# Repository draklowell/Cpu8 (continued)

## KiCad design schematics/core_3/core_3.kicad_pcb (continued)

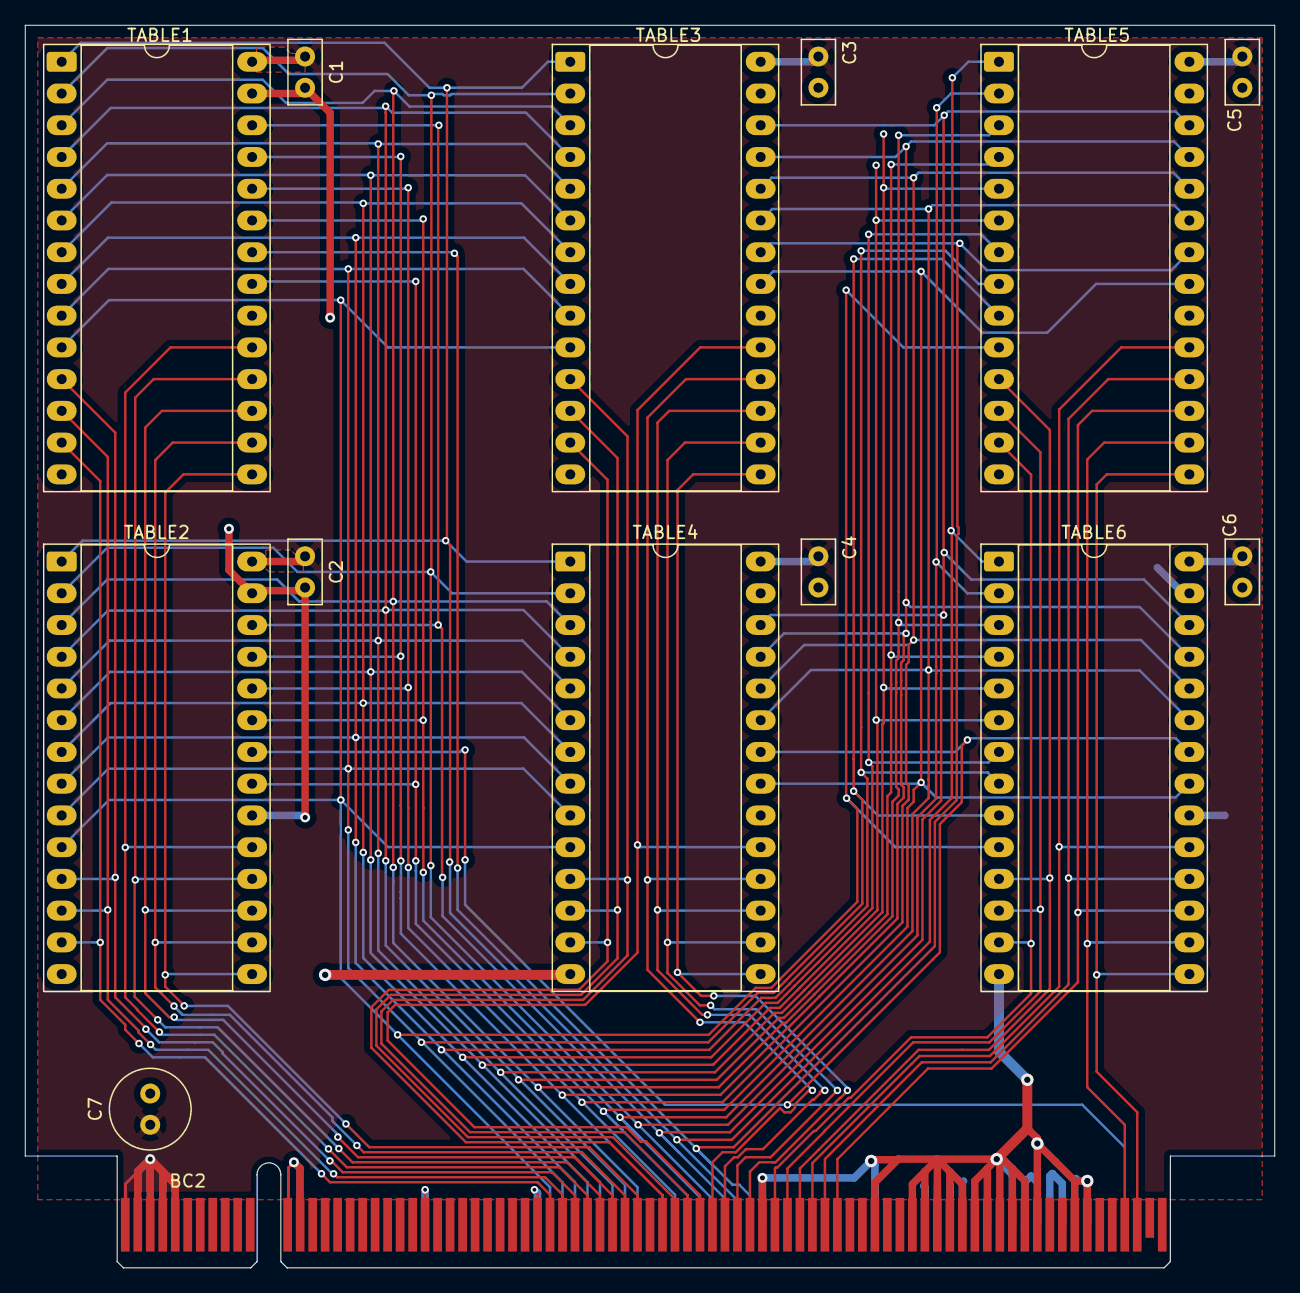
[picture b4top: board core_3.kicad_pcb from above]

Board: 2 copper layers, 100.0 x 99.4 mm, 14 parts (0 on the bottom side), 43 nets.

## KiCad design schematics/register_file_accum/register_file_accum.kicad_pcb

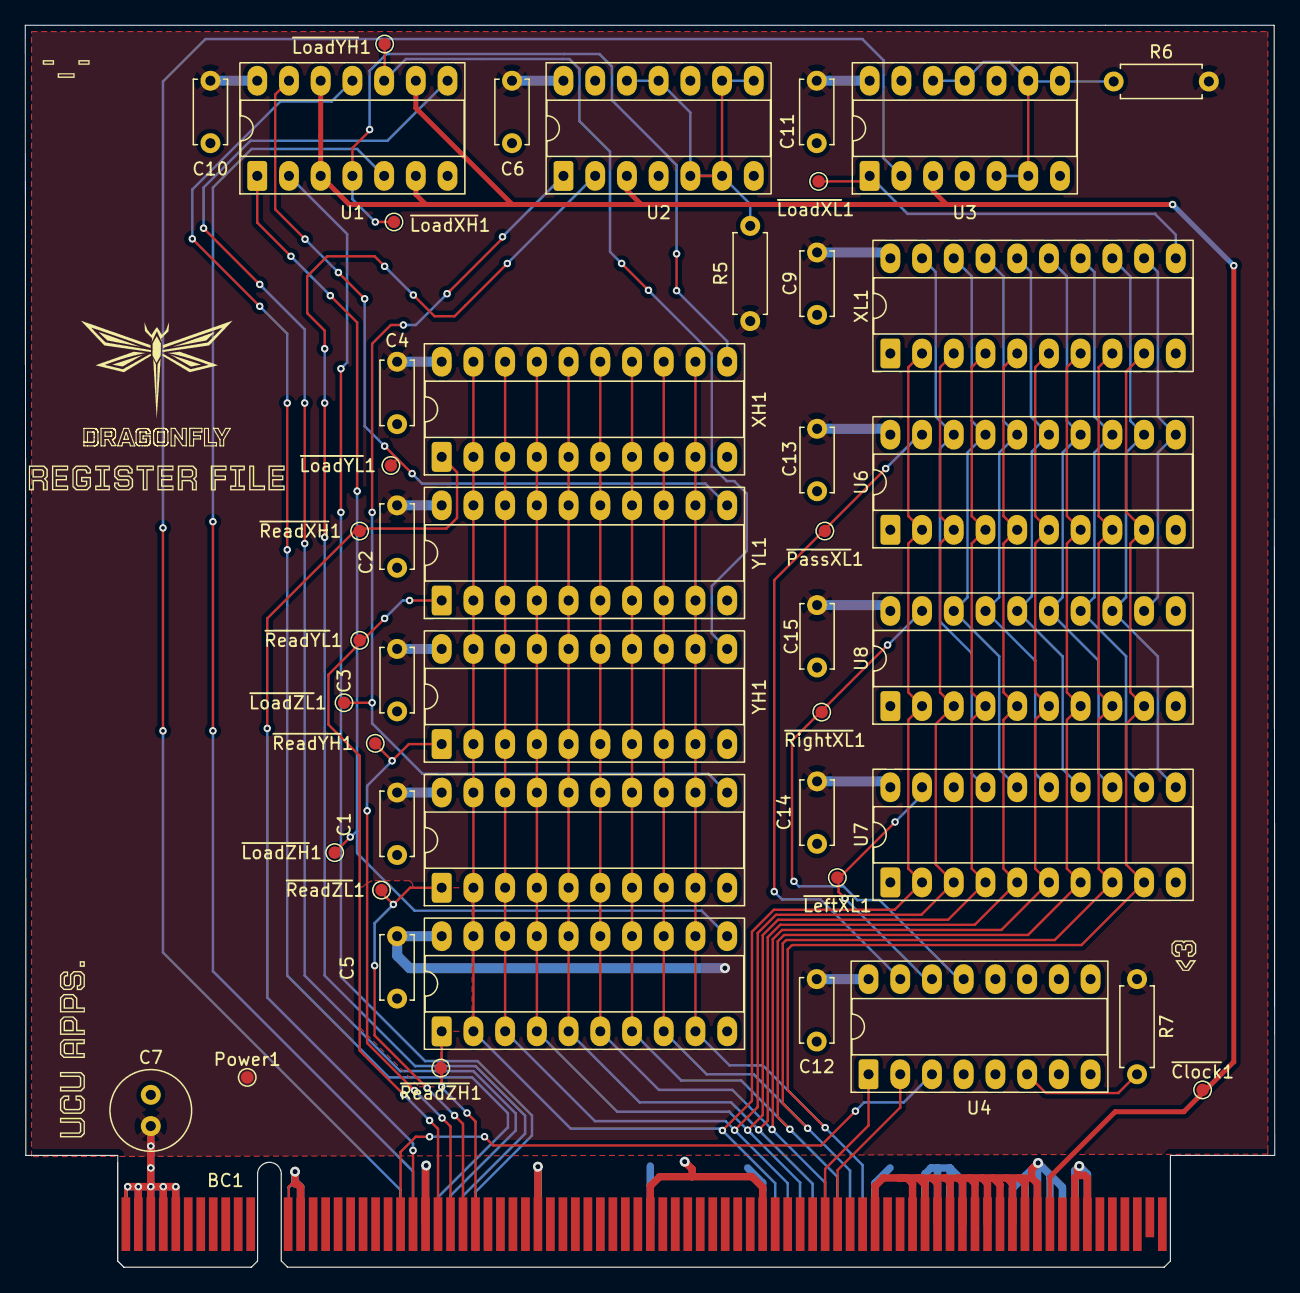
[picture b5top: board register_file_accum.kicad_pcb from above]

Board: 2 copper layers, 100.1 x 99.4 mm, 36 parts (0 on the bottom side), 45 nets.

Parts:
BC1: BusConnector; BUS_PCIexpress_x16
C1, C2, C3, C4, C5, C6, C9, C10, C11, C12, C13, C14, C15: C; C_Disc_D5.0mm_W2.5mm_P5.00mm
C7: C; C_Radial_D6.3mm_H5.0mm_P2.50mm
Power1: Power; TestPoint_Pad_D1.0mm
R5, R6, R7: R; R_Axial_DIN0207_L6.3mm_D2.5mm_P7.62mm_Horizontal
U1, U2, U3: 74LS02; DIP-14_W7.62mm_Socket_LongPads
U4: 74LS138; DIP-16_W7.62mm_Socket_LongPads
U6, U7, U8: 74LS245; DIP-20_W7.62mm_Socket_LongPads
XH1: 74LS574; DIP-20_W7.62mm_Socket_LongPads
XL1: 74LS574; DIP-20_W7.62mm_Socket_LongPads
YH1: 74LS574; DIP-20_W7.62mm_Socket_LongPads
YL1: 74LS574; DIP-20_W7.62mm_Socket_LongPads
ZH1: 74LS574; DIP-20_W7.62mm_Socket_LongPads
ZL1: 74LS574; DIP-20_W7.62mm_Socket_LongPads
kibuzzard-691DE1A7: G***; kibuzzard-691DE1A7
kibuzzard-691DE1B7: G***; kibuzzard-691DE1B7
kibuzzard-691DE19C: G***; kibuzzard-691DE19C
kibuzzard-6911B41A: G***; kibuzzard-6911B41A

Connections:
/ACCUM0: U6.18 (B0), U7.17 (B1), XL1.19 (Q0)
/ACCUM1: U6.17 (B1), U7.16 (B2), U8.18 (B0), XL1.18 (Q1)
/ACCUM2: U6.16 (B2), U7.15 (B3), U8.17 (B1), XL1.17 (Q2)
/ACCUM3: U6.15 (B3), U7.14 (B4), U8.16 (B2), XL1.16 (Q3)
/ACCUM4: U6.14 (B4), U7.13 (B5), U8.15 (B3), XL1.15 (Q4)
/ACCUM5: U6.13 (B5), U7.12 (B6), U8.14 (B4), XL1.14 (Q5)
/ACCUM6: U6.12 (B6), U7.11 (B7), U8.13 (B5), XL1.13 (Q6)
/ACCUM7: U6.11 (B7), U8.12 (B6), XL1.12 (Q7)
/ACSHLEFT: U4.14 (O1), U7.19 (CE)
/ACSHRIGHT: U4.13 (O2), U8.19 (CE)
/DATA0: BC1.A51 (DATA0), U6.2 (A0), U7.2 (A0), U8.2 (A0), XH1.2 (D0), XH1.19 (Q0), XL1.2 (D0), YH1.2 (D0), YH1.19 (Q0), YL1.2 (D0), YL1.19 (Q0), ZH1.2 (D0), ZH1.19 (Q0), ZL1.2 (D0), ZL1.19 (Q0)
/DATA1: BC1.A52 (DATA1), U6.3 (A1), U7.3 (A1), U8.3 (A1), XH1.3 (D1), XH1.18 (Q1), XL1.3 (D1), YH1.3 (D1), YH1.18 (Q1), YL1.3 (D1), YL1.18 (Q1), ZH1.3 (D1), ZH1.18 (Q1), ZL1.3 (D1), ZL1.18 (Q1)
/DATA2: BC1.A53 (DATA2), U6.4 (A2), U7.4 (A2), U8.4 (A2), XH1.4 (D2), XH1.17 (Q2), XL1.4 (D2), YH1.4 (D2), YH1.17 (Q2), YL1.4 (D2), YL1.17 (Q2), ZH1.4 (D2), ZH1.17 (Q2), ZL1.4 (D2), ZL1.17 (Q2)
/DATA3: BC1.A54 (DATA3), U6.5 (A3), U7.5 (A3), U8.5 (A3), XH1.5 (D3), XH1.16 (Q3), XL1.5 (D3), YH1.5 (D3), YH1.16 (Q3), YL1.5 (D3), YL1.16 (Q3), ZH1.5 (D3), ZH1.16 (Q3), ZL1.5 (D3), ZL1.16 (Q3)
/DATA4: BC1.A55 (DATA4), U6.6 (A4), U7.6 (A4), U8.6 (A4), XH1.6 (D4), XH1.15 (Q4), XL1.6 (D4), YH1.6 (D4), YH1.15 (Q4), YL1.6 (D4), YL1.15 (Q4), ZH1.6 (D4), ZH1.15 (Q4), ZL1.6 (D4), ZL1.15 (Q4)
/DATA5: BC1.A56 (DATA5), U6.7 (A5), U7.7 (A5), U8.7 (A5), XH1.7 (D5), XH1.14 (Q5), XL1.7 (D5), YH1.7 (D5), YH1.14 (Q5), YL1.7 (D5), YL1.14 (Q5), ZH1.7 (D5), ZH1.14 (Q5), ZL1.7 (D5), ZL1.14 (Q5)
/DATA6: BC1.A57 (DATA6), U6.8 (A6), U7.8 (A6), U8.8 (A6), XH1.8 (D6), XH1.13 (Q6), XL1.8 (D6), YH1.8 (D6), YH1.13 (Q6), YL1.8 (D6), YL1.13 (Q6), ZH1.8 (D6), ZH1.13 (Q6), ZL1.8 (D6), ZL1.13 (Q6)
/DATA7: BC1.A58 (DATA7), U6.9 (A7), U7.9 (A7), U8.9 (A7), XH1.9 (D7), XH1.12 (Q7), XL1.9 (D7), YH1.9 (D7), YH1.12 (Q7), YL1.9 (D7), YL1.12 (Q7), ZH1.9 (D7), ZH1.12 (Q7), ZL1.9 (D7), ZL1.12 (Q7)
/LAC: BC1.A21 (~LAC), U3.2
/SHL: BC1.B55 (ACSHLEFT), U4.1 (A0)
/SHR: BC1.B56 (ACSHRIGHT), U4.2 (A1)
/~CLK: BC1.B73 (~CLK), U1.3, U1.6, U1.9, U1.12, U2.3, U3.3
/~PASS: BC1.B21 (~RAC), U4.3 (A2)
/~RAC: U4.15 (O0), U6.19 (CE)
GND: BC1.A12 (GND), BC1.A13 (GND), BC1.A23 (GND), BC1.A32 (GND), BC1.A41 (GND), BC1.A50 (GND), BC1.A59 (GND), BC1.A63 (GND), BC1.A64 (GND), BC1.A65 (GND), BC1.A66 (GND), BC1.A70 (GND), BC1.A71 (GND), BC1.A72 (GND), BC1.A73 (GND), BC1.A74 (GND), BC1.A75 (GND), BC1.A76 (GND), BC1.B12 (GND), BC1.B13 (GND), BC1.B23 (GND), BC1.B32 (GND), BC1.B41 (GND), BC1.B50 (GND), BC1.B59 (GND), BC1.B62 (GND), BC1.B63 (GND), BC1.B64 (GND), BC1.B65 (GND), BC1.B66 (GND), BC1.B67 (GND), BC1.B68 (GND), BC1.B69 (GND), BC1.B70 (GND), BC1.B71 (GND), BC1.B72 (GND), BC1.B75 (GND), BC1.B76 (GND), C1.1, C2.1, C3.1, C4.1, C5.1, C6.2, C7.2, C9.2, C10.2, C11.2, C12.2, C13.2, C14.2, C15.2, U1.7 (GND), U2.7 (GND), U3.7 (GND), U4.4 (E1), U4.5 (E2), U4.8 (GND), U6.1 (A->B), U6.10 (GND), U7.1 (A->B), U7.10 (GND), U7.18 (B0), U8.1 (A->B), U8.10 (GND), U8.11 (B7), XH1.10 (GND), XL1.1 (OE), XL1.10 (GND), YH1.10 (GND), YL1.10 (GND), ZH1.10 (GND), ZL1.10 (GND)
unnamed: BC1.A22 (~LXH), U1.5
unnamed: BC1.A25 (~LYH), U1.8
unnamed: BC1.A24 (~LYL), U1.11
unnamed: BC1.A27 (~LZH), U1.2
unnamed: BC1.A26 (~LZL), U2.2
unnamed: BC1.B22 (~RXH), XH1.1 (OE)
unnamed: BC1.B25 (~RYH), YH1.1 (OE)
unnamed: BC1.B24 (~RYL), YL1.1 (OE)
unnamed: BC1.B27 (~RZH), ZH1.1 (OE)
unnamed: BC1.B26 (~RZL), ZL1.1 (OE)
unnamed: R5.2, U2.5, U2.6, U2.8, U2.9, U2.11, U2.12
unnamed: R6.1, U3.5, U3.6, U3.8, U3.9, U3.11, U3.12
unnamed: R7.2, U4.6 (E3)
unnamed: U1.4, XH1.11 (Cp)
unnamed: U3.1, XL1.11 (Cp)
unnamed: U1.10, YH1.11 (Cp)
unnamed: U1.13, YL1.11 (Cp)
unnamed: U1.1, ZH1.11 (Cp)
unnamed: U2.1, ZL1.11 (Cp)
VCC: BC1.A1 (VCC), BC1.A2 (VCC), BC1.A3 (VCC), BC1.A4 (VCC), BC1.A5 (VCC), BC1.B1 (VCC), BC1.B2 (VCC), BC1.B3 (VCC), BC1.B4 (VCC), BC1.B5 (VCC), C1.2, C2.2, C3.2, C4.2, C5.2, C6.1, C7.1, C9.1, C10.1, C11.1, C12.1, C13.1, C14.1, C15.1, Power1.1, R5.1, R6.2, R7.1, U1.14 (VCC), U2.14 (VCC), U3.14 (VCC), U4.16 (VCC), U6.20 (VCC), U7.20 (VCC), U8.20 (VCC), XH1.20 (VCC), XL1.20 (VCC), YH1.20 (VCC), YL1.20 (VCC), ZH1.20 (VCC), ZL1.20 (VCC)

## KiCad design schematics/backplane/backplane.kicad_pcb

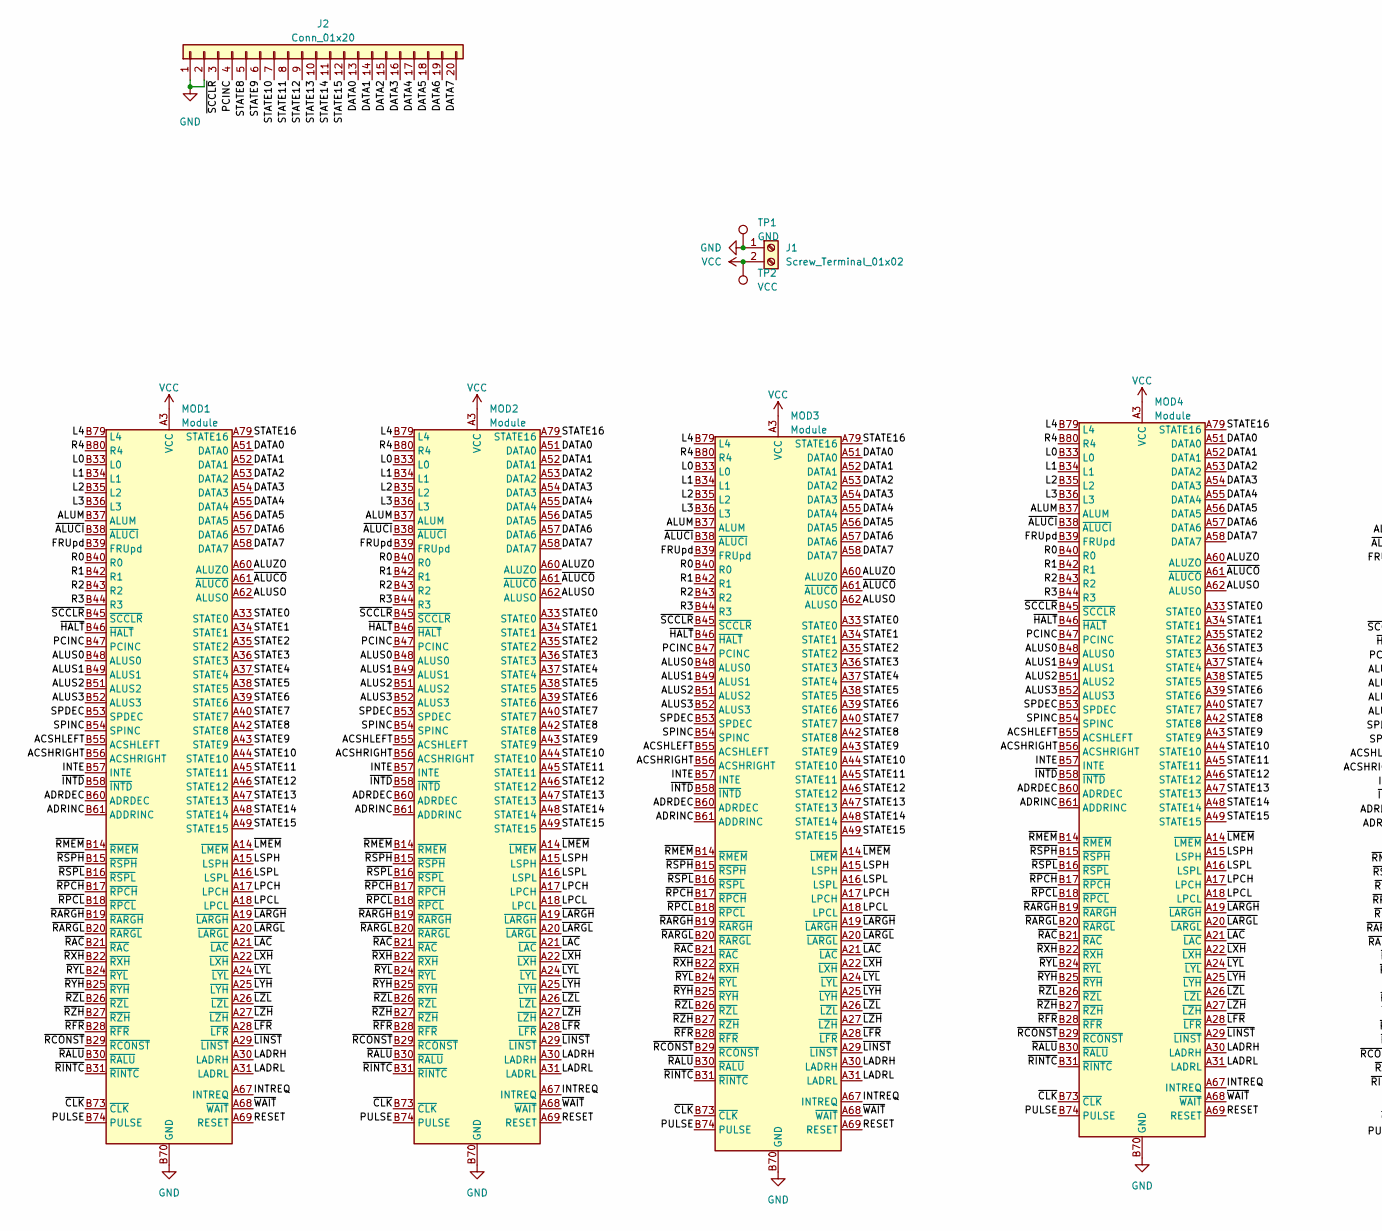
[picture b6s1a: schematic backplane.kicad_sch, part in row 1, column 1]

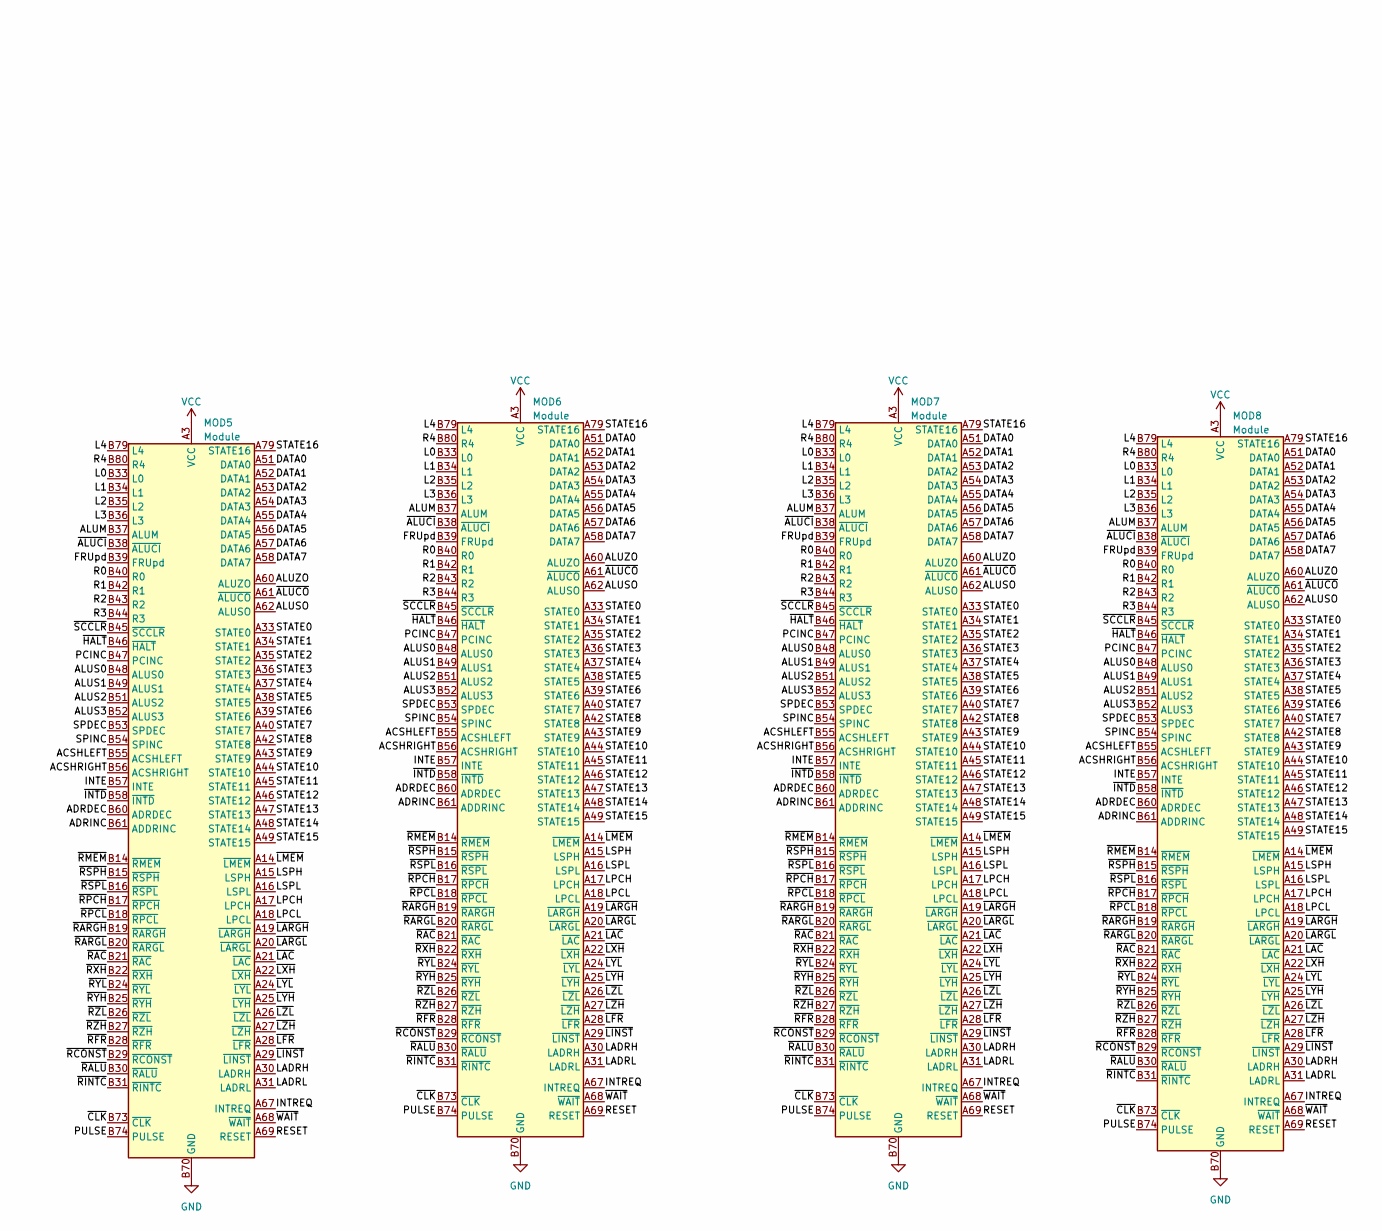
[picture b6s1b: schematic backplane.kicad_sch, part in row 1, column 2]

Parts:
J1: Screw_Terminal_01x02; SHDR2W100P0X500_1X2_1000X780X1020P
J2: Conn_01x20; PinSocket_1x20_P2.54mm_Vertical
MOD1, MOD2, MOD3, MOD4, MOD5, MOD6, MOD7, MOD8: Module; BusSlot
TP1: GND; TestPoint_Pad_D1.5mm
TP2: VCC; TestPoint_Pad_D1.5mm

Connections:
/ACSHLEFT: MOD1.B55 (ACSHLEFT), MOD2.B55 (ACSHLEFT), MOD3.B55 (ACSHLEFT), MOD4.B55 (ACSHLEFT), MOD5.B55 (ACSHLEFT), MOD6.B55 (ACSHLEFT), MOD7.B55 (ACSHLEFT), MOD8.B55 (ACSHLEFT)
/ACSHRIGHT: MOD1.B56 (ACSHRIGHT), MOD2.B56 (ACSHRIGHT), MOD3.B56 (ACSHRIGHT), MOD4.B56 (ACSHRIGHT), MOD5.B56 (ACSHRIGHT), MOD6.B56 (ACSHRIGHT), MOD7.B56 (ACSHRIGHT), MOD8.B56 (ACSHRIGHT)
/ADRDEC: MOD1.B60 (ADRDEC), MOD2.B60 (ADRDEC), MOD3.B60 (ADRDEC), MOD4.B60 (ADRDEC), MOD5.B60 (ADRDEC), MOD6.B60 (ADRDEC), MOD7.B60 (ADRDEC), MOD8.B60 (ADRDEC)
/ADRINC: MOD1.B61 (ADDRINC), MOD2.B61 (ADDRINC), MOD3.B61 (ADDRINC), MOD4.B61 (ADDRINC), MOD5.B61 (ADDRINC), MOD6.B61 (ADDRINC), MOD7.B61 (ADDRINC), MOD8.B61 (ADDRINC)
/ALUM: MOD1.B37 (ALUM), MOD2.B37 (ALUM), MOD3.B37 (ALUM), MOD4.B37 (ALUM), MOD5.B37 (ALUM), MOD6.B37 (ALUM), MOD7.B37 (ALUM), MOD8.B37 (ALUM)
/ALUS0: MOD1.B48 (ALUS0), MOD2.B48 (ALUS0), MOD3.B48 (ALUS0), MOD4.B48 (ALUS0), MOD5.B48 (ALUS0), MOD6.B48 (ALUS0), MOD7.B48 (ALUS0), MOD8.B48 (ALUS0)
/ALUS1: MOD1.B49 (ALUS1), MOD2.B49 (ALUS1), MOD3.B49 (ALUS1), MOD4.B49 (ALUS1), MOD5.B49 (ALUS1), MOD6.B49 (ALUS1), MOD7.B49 (ALUS1), MOD8.B49 (ALUS1)
/ALUS2: MOD1.B51 (ALUS2), MOD2.B51 (ALUS2), MOD3.B51 (ALUS2), MOD4.B51 (ALUS2), MOD5.B51 (ALUS2), MOD6.B51 (ALUS2), MOD7.B51 (ALUS2), MOD8.B51 (ALUS2)
/ALUS3: MOD1.B52 (ALUS3), MOD2.B52 (ALUS3), MOD3.B52 (ALUS3), MOD4.B52 (ALUS3), MOD5.B52 (ALUS3), MOD6.B52 (ALUS3), MOD7.B52 (ALUS3), MOD8.B52 (ALUS3)
/ALUSO: MOD1.A62 (ALUSO), MOD2.A62 (ALUSO), MOD3.A62 (ALUSO), MOD4.A62 (ALUSO), MOD5.A62 (ALUSO), MOD6.A62 (ALUSO), MOD7.A62 (ALUSO), MOD8.A62 (ALUSO)
/ALUZO: MOD1.A60 (ALUZO), MOD2.A60 (ALUZO), MOD3.A60 (ALUZO), MOD4.A60 (ALUZO), MOD5.A60 (ALUZO), MOD6.A60 (ALUZO), MOD7.A60 (ALUZO), MOD8.A60 (ALUZO)
/DATA0: J2.13, MOD1.A51 (DATA0), MOD2.A51 (DATA0), MOD3.A51 (DATA0), MOD4.A51 (DATA0), MOD5.A51 (DATA0), MOD6.A51 (DATA0), MOD7.A51 (DATA0), MOD8.A51 (DATA0)
/DATA1: J2.14, MOD1.A52 (DATA1), MOD2.A52 (DATA1), MOD3.A52 (DATA1), MOD4.A52 (DATA1), MOD5.A52 (DATA1), MOD6.A52 (DATA1), MOD7.A52 (DATA1), MOD8.A52 (DATA1)
/DATA2: J2.15, MOD1.A53 (DATA2), MOD2.A53 (DATA2), MOD3.A53 (DATA2), MOD4.A53 (DATA2), MOD5.A53 (DATA2), MOD6.A53 (DATA2), MOD7.A53 (DATA2), MOD8.A53 (DATA2)
/DATA3: J2.16, MOD1.A54 (DATA3), MOD2.A54 (DATA3), MOD3.A54 (DATA3), MOD4.A54 (DATA3), MOD5.A54 (DATA3), MOD6.A54 (DATA3), MOD7.A54 (DATA3), MOD8.A54 (DATA3)
/DATA4: J2.17, MOD1.A55 (DATA4), MOD2.A55 (DATA4), MOD3.A55 (DATA4), MOD4.A55 (DATA4), MOD5.A55 (DATA4), MOD6.A55 (DATA4), MOD7.A55 (DATA4), MOD8.A55 (DATA4)
/DATA5: J2.18, MOD1.A56 (DATA5), MOD2.A56 (DATA5), MOD3.A56 (DATA5), MOD4.A56 (DATA5), MOD5.A56 (DATA5), MOD6.A56 (DATA5), MOD7.A56 (DATA5), MOD8.A56 (DATA5)
/DATA6: J2.19, MOD1.A57 (DATA6), MOD2.A57 (DATA6), MOD3.A57 (DATA6), MOD4.A57 (DATA6), MOD5.A57 (DATA6), MOD6.A57 (DATA6), MOD7.A57 (DATA6), MOD8.A57 (DATA6)
/DATA7: J2.20, MOD1.A58 (DATA7), MOD2.A58 (DATA7), MOD3.A58 (DATA7), MOD4.A58 (DATA7), MOD5.A58 (DATA7), MOD6.A58 (DATA7), MOD7.A58 (DATA7), MOD8.A58 (DATA7)
/FRUpd: MOD1.B39 (FRUpd), MOD2.B39 (FRUpd), MOD3.B39 (FRUpd), MOD4.B39 (FRUpd), MOD5.B39 (FRUpd), MOD6.B39 (FRUpd), MOD7.B39 (FRUpd), MOD8.B39 (FRUpd)
/INTE: MOD1.B57 (INTE), MOD2.B57 (INTE), MOD3.B57 (INTE), MOD4.B57 (INTE), MOD5.B57 (INTE), MOD6.B57 (INTE), MOD7.B57 (INTE), MOD8.B57 (INTE)
/INTREQ: MOD1.A67 (INTREQ), MOD2.A67 (INTREQ), MOD3.A67 (INTREQ), MOD4.A67 (INTREQ), MOD5.A67 (INTREQ), MOD6.A67 (INTREQ), MOD7.A67 (INTREQ), MOD8.A67 (INTREQ)
/L0: MOD1.B33 (L0), MOD2.B33 (L0), MOD3.B33 (L0), MOD4.B33 (L0), MOD5.B33 (L0), MOD6.B33 (L0), MOD7.B33 (L0), MOD8.B33 (L0)
/L1: MOD1.B34 (L1), MOD2.B34 (L1), MOD3.B34 (L1), MOD4.B34 (L1), MOD5.B34 (L1), MOD6.B34 (L1), MOD7.B34 (L1), MOD8.B34 (L1)
/L2: MOD1.B35 (L2), MOD2.B35 (L2), MOD3.B35 (L2), MOD4.B35 (L2), MOD5.B35 (L2), MOD6.B35 (L2), MOD7.B35 (L2), MOD8.B35 (L2)
/L3: MOD1.B36 (L3), MOD2.B36 (L3), MOD3.B36 (L3), MOD4.B36 (L3), MOD5.B36 (L3), MOD6.B36 (L3), MOD7.B36 (L3), MOD8.B36 (L3)
/L4: MOD1.B79 (L4), MOD2.B79 (L4), MOD3.B79 (L4), MOD4.B79 (L4), MOD5.B79 (L4), MOD6.B79 (L4), MOD7.B79 (L4), MOD8.B79 (L4)
/LADRH: MOD1.A30 (LADRH), MOD2.A30 (LADRH), MOD3.A30 (LADRH), MOD4.A30 (LADRH), MOD5.A30 (LADRH), MOD6.A30 (LADRH), MOD7.A30 (LADRH), MOD8.A30 (LADRH)
/LADRL: MOD1.A31 (LADRL), MOD2.A31 (LADRL), MOD3.A31 (LADRL), MOD4.A31 (LADRL), MOD5.A31 (LADRL), MOD6.A31 (LADRL), MOD7.A31 (LADRL), MOD8.A31 (LADRL)
/LPCH: MOD1.A17 (LPCH), MOD2.A17 (LPCH), MOD3.A17 (LPCH), MOD4.A17 (LPCH), MOD5.A17 (LPCH), MOD6.A17 (LPCH), MOD7.A17 (LPCH), MOD8.A17 (LPCH)
/LPCL: MOD1.A18 (LPCL), MOD2.A18 (LPCL), MOD3.A18 (LPCL), MOD4.A18 (LPCL), MOD5.A18 (LPCL), MOD6.A18 (LPCL), MOD7.A18 (LPCL), MOD8.A18 (LPCL)
/LSPH: MOD1.A15 (LSPH), MOD2.A15 (LSPH), MOD3.A15 (LSPH), MOD4.A15 (LSPH), MOD5.A15 (LSPH), MOD6.A15 (LSPH), MOD7.A15 (LSPH), MOD8.A15 (LSPH)
/LSPL: MOD1.A16 (LSPL), MOD2.A16 (LSPL), MOD3.A16 (LSPL), MOD4.A16 (LSPL), MOD5.A16 (LSPL), MOD6.A16 (LSPL), MOD7.A16 (LSPL), MOD8.A16 (LSPL)
/PCINC: J2.4, MOD1.B47 (PCINC), MOD2.B47 (PCINC), MOD3.B47 (PCINC), MOD4.B47 (PCINC), MOD5.B47 (PCINC), MOD6.B47 (PCINC), MOD7.B47 (PCINC), MOD8.B47 (PCINC)
/PULSE: MOD1.B74 (PULSE), MOD2.B74 (PULSE), MOD3.B74 (PULSE), MOD4.B74 (PULSE), MOD5.B74 (PULSE), MOD6.B74 (PULSE), MOD7.B74 (PULSE), MOD8.B74 (PULSE)
/R0: MOD1.B40 (R0), MOD2.B40 (R0), MOD3.B40 (R0), MOD4.B40 (R0), MOD5.B40 (R0), MOD6.B40 (R0), MOD7.B40 (R0), MOD8.B40 (R0)
/R1: MOD1.B42 (R1), MOD2.B42 (R1), MOD3.B42 (R1), MOD4.B42 (R1), MOD5.B42 (R1), MOD6.B42 (R1), MOD7.B42 (R1), MOD8.B42 (R1)
/R2: MOD1.B43 (R2), MOD2.B43 (R2), MOD3.B43 (R2), MOD4.B43 (R2), MOD5.B43 (R2), MOD6.B43 (R2), MOD7.B43 (R2), MOD8.B43 (R2)
/R3: MOD1.B44 (R3), MOD2.B44 (R3), MOD3.B44 (R3), MOD4.B44 (R3), MOD5.B44 (R3), MOD6.B44 (R3), MOD7.B44 (R3), MOD8.B44 (R3)
/R4: MOD1.B80 (R4), MOD2.B80 (R4), MOD3.B80 (R4), MOD4.B80 (R4), MOD5.B80 (R4), MOD6.B80 (R4), MOD7.B80 (R4), MOD8.B80 (R4)
/RESET: MOD1.A69 (RESET), MOD2.A69 (RESET), MOD3.A69 (RESET), MOD4.A69 (RESET), MOD5.A69 (RESET), MOD6.A69 (RESET), MOD7.A69 (RESET), MOD8.A69 (RESET)
/SPDEC: MOD1.B53 (SPDEC), MOD2.B53 (SPDEC), MOD3.B53 (SPDEC), MOD4.B53 (SPDEC), MOD5.B53 (SPDEC), MOD6.B53 (SPDEC), MOD7.B53 (SPDEC), MOD8.B53 (SPDEC)
/SPINC: MOD1.B54 (SPINC), MOD2.B54 (SPINC), MOD3.B54 (SPINC), MOD4.B54 (SPINC), MOD5.B54 (SPINC), MOD6.B54 (SPINC), MOD7.B54 (SPINC), MOD8.B54 (SPINC)
/STATE0: MOD1.A33 (STATE0), MOD2.A33 (STATE0), MOD3.A33 (STATE0), MOD4.A33 (STATE0), MOD5.A33 (STATE0), MOD6.A33 (STATE0), MOD7.A33 (STATE0), MOD8.A33 (STATE0)
/STATE1: MOD1.A34 (STATE1), MOD2.A34 (STATE1), MOD3.A34 (STATE1), MOD4.A34 (STATE1), MOD5.A34 (STATE1), MOD6.A34 (STATE1), MOD7.A34 (STATE1), MOD8.A34 (STATE1)
/STATE2: MOD1.A35 (STATE2), MOD2.A35 (STATE2), MOD3.A35 (STATE2), MOD4.A35 (STATE2), MOD5.A35 (STATE2), MOD6.A35 (STATE2), MOD7.A35 (STATE2), MOD8.A35 (STATE2)
/STATE3: MOD1.A36 (STATE3), MOD2.A36 (STATE3), MOD3.A36 (STATE3), MOD4.A36 (STATE3), MOD5.A36 (STATE3), MOD6.A36 (STATE3), MOD7.A36 (STATE3), MOD8.A36 (STATE3)
/STATE4: MOD1.A37 (STATE4), MOD2.A37 (STATE4), MOD3.A37 (STATE4), MOD4.A37 (STATE4), MOD5.A37 (STATE4), MOD6.A37 (STATE4), MOD7.A37 (STATE4), MOD8.A37 (STATE4)
/STATE5: MOD1.A38 (STATE5), MOD2.A38 (STATE5), MOD3.A38 (STATE5), MOD4.A38 (STATE5), MOD5.A38 (STATE5), MOD6.A38 (STATE5), MOD7.A38 (STATE5), MOD8.A38 (STATE5)
/STATE6: MOD1.A39 (STATE6), MOD2.A39 (STATE6), MOD3.A39 (STATE6), MOD4.A39 (STATE6), MOD5.A39 (STATE6), MOD6.A39 (STATE6), MOD7.A39 (STATE6), MOD8.A39 (STATE6)
/STATE7: MOD1.A40 (STATE7), MOD2.A40 (STATE7), MOD3.A40 (STATE7), MOD4.A40 (STATE7), MOD5.A40 (STATE7), MOD6.A40 (STATE7), MOD7.A40 (STATE7), MOD8.A40 (STATE7)
/STATE8: J2.5, MOD1.A42 (STATE8), MOD2.A42 (STATE8), MOD3.A42 (STATE8), MOD4.A42 (STATE8), MOD5.A42 (STATE8), MOD6.A42 (STATE8), MOD7.A42 (STATE8), MOD8.A42 (STATE8)
/STATE9: J2.6, MOD1.A43 (STATE9), MOD2.A43 (STATE9), MOD3.A43 (STATE9), MOD4.A43 (STATE9), MOD5.A43 (STATE9), MOD6.A43 (STATE9), MOD7.A43 (STATE9), MOD8.A43 (STATE9)
/STATE10: J2.7, MOD1.A44 (STATE10), MOD2.A44 (STATE10), MOD3.A44 (STATE10), MOD4.A44 (STATE10), MOD5.A44 (STATE10), MOD6.A44 (STATE10), MOD7.A44 (STATE10), MOD8.A44 (STATE10)
/STATE11: J2.8, MOD1.A45 (STATE11), MOD2.A45 (STATE11), MOD3.A45 (STATE11), MOD4.A45 (STATE11), MOD5.A45 (STATE11), MOD6.A45 (STATE11), MOD7.A45 (STATE11), MOD8.A45 (STATE11)
/STATE12: J2.9, MOD1.A46 (STATE12), MOD2.A46 (STATE12), MOD3.A46 (STATE12), MOD4.A46 (STATE12), MOD5.A46 (STATE12), MOD6.A46 (STATE12), MOD7.A46 (STATE12), MOD8.A46 (STATE12)
/STATE13: J2.10, MOD1.A47 (STATE13), MOD2.A47 (STATE13), MOD3.A47 (STATE13), MOD4.A47 (STATE13), MOD5.A47 (STATE13), MOD6.A47 (STATE13), MOD7.A47 (STATE13), MOD8.A47 (STATE13)
/STATE14: J2.11, MOD1.A48 (STATE14), MOD2.A48 (STATE14), MOD3.A48 (STATE14), MOD4.A48 (STATE14), MOD5.A48 (STATE14), MOD6.A48 (STATE14), MOD7.A48 (STATE14), MOD8.A48 (STATE14)
/STATE15: J2.12, MOD1.A49 (STATE15), MOD2.A49 (STATE15), MOD3.A49 (STATE15), MOD4.A49 (STATE15), MOD5.A49 (STATE15), MOD6.A49 (STATE15), MOD7.A49 (STATE15), MOD8.A49 (STATE15)
/STATE16: MOD1.A79 (STATE16), MOD2.A79 (STATE16), MOD3.A79 (STATE16), MOD4.A79 (STATE16), MOD5.A79 (STATE16), MOD6.A79 (STATE16), MOD7.A79 (STATE16), MOD8.A79 (STATE16)
/~ALUCI: MOD1.B38 (~ALUCI), MOD2.B38 (~ALUCI), MOD3.B38 (~ALUCI), MOD4.B38 (~ALUCI), MOD5.B38 (~ALUCI), MOD6.B38 (~ALUCI), MOD7.B38 (~ALUCI), MOD8.B38 (~ALUCI)
/~ALUCO: MOD1.A61 (~ALUCO), MOD2.A61 (~ALUCO), MOD3.A61 (~ALUCO), MOD4.A61 (~ALUCO), MOD5.A61 (~ALUCO), MOD6.A61 (~ALUCO), MOD7.A61 (~ALUCO), MOD8.A61 (~ALUCO)
/~CLK: MOD1.B73 (~CLK), MOD2.B73 (~CLK), MOD3.B73 (~CLK), MOD4.B73 (~CLK), MOD5.B73 (~CLK), MOD6.B73 (~CLK), MOD7.B73 (~CLK), MOD8.B73 (~CLK)
/~HALT: MOD1.B46 (~HALT), MOD2.B46 (~HALT), MOD3.B46 (~HALT), MOD4.B46 (~HALT), MOD5.B46 (~HALT), MOD6.B46 (~HALT), MOD7.B46 (~HALT), MOD8.B46 (~HALT)
/~INTD: MOD1.B58 (~INTD), MOD2.B58 (~INTD), MOD3.B58 (~INTD), MOD4.B58 (~INTD), MOD5.B58 (~INTD), MOD6.B58 (~INTD), MOD7.B58 (~INTD), MOD8.B58 (~INTD)
/~LAC: MOD1.A21 (~LAC), MOD2.A21 (~LAC), MOD3.A21 (~LAC), MOD4.A21 (~LAC), MOD5.A21 (~LAC), MOD6.A21 (~LAC), MOD7.A21 (~LAC), MOD8.A21 (~LAC)
/~LARGH: MOD1.A19 (~LARGH), MOD2.A19 (~LARGH), MOD3.A19 (~LARGH), MOD4.A19 (~LARGH), MOD5.A19 (~LARGH), MOD6.A19 (~LARGH), MOD7.A19 (~LARGH), MOD8.A19 (~LARGH)
/~LARGL: MOD1.A20 (~LARGL), MOD2.A20 (~LARGL), MOD3.A20 (~LARGL), MOD4.A20 (~LARGL), MOD5.A20 (~LARGL), MOD6.A20 (~LARGL), MOD7.A20 (~LARGL), MOD8.A20 (~LARGL)
/~LFR: MOD1.A28 (~LFR), MOD2.A28 (~LFR), MOD3.A28 (~LFR), MOD4.A28 (~LFR), MOD5.A28 (~LFR), MOD6.A28 (~LFR), MOD7.A28 (~LFR), MOD8.A28 (~LFR)
/~LINST: MOD1.A29 (~LINST), MOD2.A29 (~LINST), MOD3.A29 (~LINST), MOD4.A29 (~LINST), MOD5.A29 (~LINST), MOD6.A29 (~LINST), MOD7.A29 (~LINST), MOD8.A29 (~LINST)
/~LMEM: MOD1.A14 (~LMEM), MOD2.A14 (~LMEM), MOD3.A14 (~LMEM), MOD4.A14 (~LMEM), MOD5.A14 (~LMEM), MOD6.A14 (~LMEM), MOD7.A14 (~LMEM), MOD8.A14 (~LMEM)
/~LXH: MOD1.A22 (~LXH), MOD2.A22 (~LXH), MOD3.A22 (~LXH), MOD4.A22 (~LXH), MOD5.A22 (~LXH), MOD6.A22 (~LXH), MOD7.A22 (~LXH), MOD8.A22 (~LXH)
/~LYH: MOD1.A25 (~LYH), MOD2.A25 (~LYH), MOD3.A25 (~LYH), MOD4.A25 (~LYH), MOD5.A25 (~LYH), MOD6.A25 (~LYH), MOD7.A25 (~LYH), MOD8.A25 (~LYH)
/~LYL: MOD1.A24 (~LYL), MOD2.A24 (~LYL), MOD3.A24 (~LYL), MOD4.A24 (~LYL), MOD5.A24 (~LYL), MOD6.A24 (~LYL), MOD7.A24 (~LYL), MOD8.A24 (~LYL)
/~LZH: MOD1.A27 (~LZH), MOD2.A27 (~LZH), MOD3.A27 (~LZH), MOD4.A27 (~LZH), MOD5.A27 (~LZH), MOD6.A27 (~LZH), MOD7.A27 (~LZH), MOD8.A27 (~LZH)
/~LZL: MOD1.A26 (~LZL), MOD2.A26 (~LZL), MOD3.A26 (~LZL), MOD4.A26 (~LZL), MOD5.A26 (~LZL), MOD6.A26 (~LZL), MOD7.A26 (~LZL), MOD8.A26 (~LZL)
/~RAC: MOD1.B21 (~RAC), MOD2.B21 (~RAC), MOD3.B21 (~RAC), MOD4.B21 (~RAC), MOD5.B21 (~RAC), MOD6.B21 (~RAC), MOD7.B21 (~RAC), MOD8.B21 (~RAC)
/~RALU: MOD1.B30 (~RALU), MOD2.B30 (~RALU), MOD3.B30 (~RALU), MOD4.B30 (~RALU), MOD5.B30 (~RALU), MOD6.B30 (~RALU), MOD7.B30 (~RALU), MOD8.B30 (~RALU)
/~RARGH: MOD1.B19 (~RARGH), MOD2.B19 (~RARGH), MOD3.B19 (~RARGH), MOD4.B19 (~RARGH), MOD5.B19 (~RARGH), MOD6.B19 (~RARGH), MOD7.B19 (~RARGH), MOD8.B19 (~RARGH)
/~RARGL: MOD1.B20 (~RARGL), MOD2.B20 (~RARGL), MOD3.B20 (~RARGL), MOD4.B20 (~RARGL), MOD5.B20 (~RARGL), MOD6.B20 (~RARGL), MOD7.B20 (~RARGL), MOD8.B20 (~RARGL)
/~RCONST: MOD1.B29 (~RCONST), MOD2.B29 (~RCONST), MOD3.B29 (~RCONST), MOD4.B29 (~RCONST), MOD5.B29 (~RCONST), MOD6.B29 (~RCONST), MOD7.B29 (~RCONST), MOD8.B29 (~RCONST)
/~RFR: MOD1.B28 (~RFR), MOD2.B28 (~RFR), MOD3.B28 (~RFR), MOD4.B28 (~RFR), MOD5.B28 (~RFR), MOD6.B28 (~RFR), MOD7.B28 (~RFR), MOD8.B28 (~RFR)
/~RINTC: MOD1.B31 (~RINTC), MOD2.B31 (~RINTC), MOD3.B31 (~RINTC), MOD4.B31 (~RINTC), MOD5.B31 (~RINTC), MOD6.B31 (~RINTC), MOD7.B31 (~RINTC), MOD8.B31 (~RINTC)
/~RMEM: MOD1.B14 (~RMEM), MOD2.B14 (~RMEM), MOD3.B14 (~RMEM), MOD4.B14 (~RMEM), MOD5.B14 (~RMEM), MOD6.B14 (~RMEM), MOD7.B14 (~RMEM), MOD8.B14 (~RMEM)
/~RPCH: MOD1.B17 (~RPCH), MOD2.B17 (~RPCH), MOD3.B17 (~RPCH), MOD4.B17 (~RPCH), MOD5.B17 (~RPCH), MOD6.B17 (~RPCH), MOD7.B17 (~RPCH), MOD8.B17 (~RPCH)
/~RPCL: MOD1.B18 (~RPCL), MOD2.B18 (~RPCL), MOD3.B18 (~RPCL), MOD4.B18 (~RPCL), MOD5.B18 (~RPCL), MOD6.B18 (~RPCL), MOD7.B18 (~RPCL), MOD8.B18 (~RPCL)
/~RSPH: MOD1.B15 (~RSPH), MOD2.B15 (~RSPH), MOD3.B15 (~RSPH), MOD4.B15 (~RSPH), MOD5.B15 (~RSPH), MOD6.B15 (~RSPH), MOD7.B15 (~RSPH), MOD8.B15 (~RSPH)
/~RSPL: MOD1.B16 (~RSPL), MOD2.B16 (~RSPL), MOD3.B16 (~RSPL), MOD4.B16 (~RSPL), MOD5.B16 (~RSPL), MOD6.B16 (~RSPL), MOD7.B16 (~RSPL), MOD8.B16 (~RSPL)
/~RXH: MOD1.B22 (~RXH), MOD2.B22 (~RXH), MOD3.B22 (~RXH), MOD4.B22 (~RXH), MOD5.B22 (~RXH), MOD6.B22 (~RXH), MOD7.B22 (~RXH), MOD8.B22 (~RXH)
/~RYH: MOD1.B25 (~RYH), MOD2.B25 (~RYH), MOD3.B25 (~RYH), MOD4.B25 (~RYH), MOD5.B25 (~RYH), MOD6.B25 (~RYH), MOD7.B25 (~RYH), MOD8.B25 (~RYH)
/~RYL: MOD1.B24 (~RYL), MOD2.B24 (~RYL), MOD3.B24 (~RYL), MOD4.B24 (~RYL), MOD5.B24 (~RYL), MOD6.B24 (~RYL), MOD7.B24 (~RYL), MOD8.B24 (~RYL)
/~RZH: MOD1.B27 (~RZH), MOD2.B27 (~RZH), MOD3.B27 (~RZH), MOD4.B27 (~RZH), MOD5.B27 (~RZH), MOD6.B27 (~RZH), MOD7.B27 (~RZH), MOD8.B27 (~RZH)
/~RZL: MOD1.B26 (~RZL), MOD2.B26 (~RZL), MOD3.B26 (~RZL), MOD4.B26 (~RZL), MOD5.B26 (~RZL), MOD6.B26 (~RZL), MOD7.B26 (~RZL), MOD8.B26 (~RZL)
/~SCCLR: J2.3, MOD1.B45 (~SCCLR), MOD2.B45 (~SCCLR), MOD3.B45 (~SCCLR), MOD4.B45 (~SCCLR), MOD5.B45 (~SCCLR), MOD6.B45 (~SCCLR), MOD7.B45 (~SCCLR), MOD8.B45 (~SCCLR)
/~WAIT: MOD1.A68 (~WAIT), MOD2.A68 (~WAIT), MOD3.A68 (~WAIT), MOD4.A68 (~WAIT), MOD5.A68 (~WAIT), MOD6.A68 (~WAIT), MOD7.A68 (~WAIT), MOD8.A68 (~WAIT)
GND: J1.1, J2.1, J2.2, MOD1.A12 (GND), MOD1.A13 (GND), MOD1.A23 (GND), MOD1.A32 (GND), MOD1.A41 (GND), MOD1.A50 (GND), MOD1.A59 (GND), MOD1.A63 (GND), MOD1.A64 (GND), MOD1.A65 (GND), MOD1.A66 (GND), MOD1.A70 (GND), MOD1.A71 (GND), MOD1.A72 (GND), MOD1.A73 (GND), MOD1.A74 (GND), MOD1.A75 (GND), MOD1.A76 (GND), MOD1.B12 (GND), MOD1.B13 (GND), MOD1.B23 (GND), MOD1.B32 (GND), MOD1.B41 (GND), MOD1.B50 (GND), MOD1.B59 (GND), MOD1.B62 (GND), MOD1.B63 (GND), MOD1.B64 (GND), MOD1.B65 (GND), MOD1.B66 (GND), MOD1.B67 (GND), MOD1.B68 (GND), MOD1.B69 (GND), MOD1.B70 (GND), MOD1.B71 (GND), MOD1.B72 (GND), MOD1.B75 (GND), MOD1.B76 (GND), MOD2.A12 (GND), MOD2.A13 (GND), MOD2.A23 (GND), MOD2.A32 (GND), MOD2.A41 (GND), MOD2.A50 (GND), MOD2.A59 (GND), MOD2.A63 (GND), MOD2.A64 (GND), MOD2.A65 (GND), MOD2.A66 (GND), MOD2.A70 (GND), MOD2.A71 (GND), MOD2.A72 (GND), MOD2.A73 (GND), MOD2.A74 (GND), MOD2.A75 (GND), MOD2.A76 (GND), MOD2.B12 (GND), MOD2.B13 (GND), MOD2.B23 (GND), MOD2.B32 (GND), MOD2.B41 (GND), MOD2.B50 (GND), MOD2.B59 (GND), MOD2.B62 (GND), MOD2.B63 (GND), MOD2.B64 (GND), MOD2.B65 (GND), MOD2.B66 (GND), MOD2.B67 (GND), MOD2.B68 (GND), MOD2.B69 (GND), MOD2.B70 (GND), MOD2.B71 (GND), MOD2.B72 (GND), MOD2.B75 (GND), MOD2.B76 (GND), MOD3.A12 (GND), MOD3.A13 (GND), MOD3.A23 (GND), MOD3.A32 (GND), MOD3.A41 (GND), MOD3.A50 (GND), MOD3.A59 (GND), MOD3.A63 (GND), MOD3.A64 (GND), MOD3.A65 (GND), MOD3.A66 (GND), MOD3.A70 (GND), MOD3.A71 (GND), MOD3.A72 (GND), MOD3.A73 (GND), MOD3.A74 (GND), MOD3.A75 (GND), MOD3.A76 (GND), MOD3.B12 (GND), MOD3.B13 (GND), MOD3.B23 (GND), MOD3.B32 (GND), MOD3.B41 (GND), MOD3.B50 (GND), MOD3.B59 (GND), MOD3.B62 (GND), MOD3.B63 (GND), MOD3.B64 (GND), MOD3.B65 (GND), MOD3.B66 (GND), MOD3.B67 (GND), MOD3.B68 (GND), MOD3.B69 (GND), MOD3.B70 (GND), MOD3.B71 (GND), MOD3.B72 (GND), MOD3.B75 (GND), MOD3.B76 (GND), MOD4.A12 (GND), MOD4.A13 (GND), MOD4.A23 (GND), MOD4.A32 (GND), MOD4.A41 (GND), MOD4.A50 (GND), MOD4.A59 (GND), MOD4.A63 (GND), MOD4.A64 (GND), MOD4.A65 (GND), MOD4.A66 (GND), MOD4.A70 (GND), MOD4.A71 (GND), MOD4.A72 (GND), MOD4.A73 (GND), MOD4.A74 (GND), MOD4.A75 (GND), MOD4.A76 (GND), MOD4.B12 (GND), MOD4.B13 (GND), MOD4.B23 (GND), MOD4.B32 (GND), MOD4.B41 (GND), MOD4.B50 (GND), MOD4.B59 (GND), MOD4.B62 (GND), MOD4.B63 (GND), MOD4.B64 (GND), MOD4.B65 (GND), MOD4.B66 (GND), MOD4.B67 (GND), MOD4.B68 (GND), MOD4.B69 (GND), MOD4.B70 (GND), MOD4.B71 (GND), MOD4.B72 (GND), MOD4.B75 (GND), MOD4.B76 (GND), MOD5.A12 (GND), MOD5.A13 (GND), MOD5.A23 (GND), MOD5.A32 (GND), MOD5.A41 (GND), MOD5.A50 (GND), MOD5.A59 (GND), MOD5.A63 (GND), MOD5.A64 (GND), MOD5.A65 (GND), MOD5.A66 (GND), MOD5.A70 (GND), MOD5.A71 (GND), MOD5.A72 (GND), MOD5.A73 (GND), MOD5.A74 (GND), MOD5.A75 (GND), MOD5.A76 (GND), MOD5.B12 (GND), MOD5.B13 (GND), MOD5.B23 (GND), MOD5.B32 (GND), MOD5.B41 (GND), MOD5.B50 (GND), MOD5.B59 (GND), MOD5.B62 (GND), MOD5.B63 (GND), MOD5.B64 (GND), MOD5.B65 (GND), MOD5.B66 (GND), MOD5.B67 (GND), MOD5.B68 (GND), MOD5.B69 (GND), MOD5.B70 (GND), MOD5.B71 (GND), MOD5.B72 (GND), MOD5.B75 (GND), MOD5.B76 (GND), MOD6.A12 (GND), MOD6.A13 (GND), MOD6.A23 (GND), MOD6.A32 (GND), MOD6.A41 (GND), MOD6.A50 (GND), MOD6.A59 (GND), MOD6.A63 (GND), MOD6.A64 (GND), MOD6.A65 (GND), MOD6.A66 (GND), MOD6.A70 (GND), MOD6.A71 (GND), MOD6.A72 (GND), MOD6.A73 (GND), MOD6.A74 (GND), MOD6.A75 (GND), MOD6.A76 (GND), MOD6.B12 (GND), MOD6.B13 (GND), MOD6.B23 (GND), MOD6.B32 (GND), MOD6.B41 (GND), MOD6.B50 (GND), MOD6.B59 (GND), MOD6.B62 (GND), MOD6.B63 (GND), MOD6.B64 (GND), MOD6.B65 (GND), MOD6.B66 (GND), MOD6.B67 (GND), MOD6.B68 (GND), MOD6.B69 (GND), MOD6.B70 (GND), MOD6.B71 (GND), MOD6.B72 (GND), MOD6.B75 (GND), MOD6.B76 (GND), MOD7.A12 (GND), MOD7.A13 (GND), MOD7.A23 (GND), MOD7.A32 (GND), MOD7.A41 (GND), MOD7.A50 (GND), MOD7.A59 (GND), MOD7.A63 (GND), MOD7.A64 (GND), MOD7.A65 (GND), MOD7.A66 (GND), MOD7.A70 (GND), MOD7.A71 (GND), MOD7.A72 (GND), MOD7.A73 (GND), MOD7.A74 (GND), MOD7.A75 (GND), MOD7.A76 (GND), MOD7.B12 (GND), MOD7.B13 (GND), MOD7.B23 (GND), MOD7.B32 (GND), MOD7.B41 (GND), MOD7.B50 (GND), MOD7.B59 (GND), MOD7.B62 (GND), MOD7.B63 (GND), MOD7.B64 (GND), MOD7.B65 (GND), MOD7.B66 (GND), MOD7.B67 (GND), MOD7.B68 (GND), MOD7.B69 (GND), MOD7.B70 (GND)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
VCC: J1.2, MOD1.A1 (VCC), MOD1.A2 (VCC), MOD1.A3 (VCC), MOD1.A4 (VCC), MOD1.A5 (VCC), MOD1.B1 (VCC), MOD1.B2 (VCC), MOD1.B3 (VCC), MOD1.B4 (VCC), MOD1.B5 (VCC), MOD2.A1 (VCC), MOD2.A2 (VCC), MOD2.A3 (VCC), MOD2.A4 (VCC), MOD2.A5 (VCC), MOD2.B1 (VCC), MOD2.B2 (VCC), MOD2.B3 (VCC), MOD2.B4 (VCC), MOD2.B5 (VCC), MOD3.A1 (VCC), MOD3.A2 (VCC), MOD3.A3 (VCC), MOD3.A4 (VCC), MOD3.A5 (VCC), MOD3.B1 (VCC), MOD3.B2 (VCC), MOD3.B3 (VCC), MOD3.B4 (VCC), MOD3.B5 (VCC), MOD4.A1 (VCC), MOD4.A2 (VCC), MOD4.A3 (VCC), MOD4.A4 (VCC), MOD4.A5 (VCC), MOD4.B1 (VCC), MOD4.B2 (VCC), MOD4.B3 (VCC), MOD4.B4 (VCC), MOD4.B5 (VCC), MOD5.A1 (VCC), MOD5.A2 (VCC), MOD5.A3 (VCC), MOD5.A4 (VCC), MOD5.A5 (VCC), MOD5.B1 (VCC), MOD5.B2 (VCC), MOD5.B3 (VCC), MOD5.B4 (VCC), MOD5.B5 (VCC), MOD6.A1 (VCC), MOD6.A2 (VCC), MOD6.A3 (VCC), MOD6.A4 (VCC), MOD6.A5 (VCC), MOD6.B1 (VCC), MOD6.B2 (VCC), MOD6.B3 (VCC), MOD6.B4 (VCC), MOD6.B5 (VCC), MOD7.A1 (VCC), MOD7.A2 (VCC), MOD7.A3 (VCC), MOD7.A4 (VCC), MOD7.A5 (VCC), MOD7.B1 (VCC), MOD7.B2 (VCC), MOD7.B3 (VCC), MOD7.B4 (VCC), MOD7.B5 (VCC), MOD8.A1 (VCC), MOD8.A2 (VCC), MOD8.A3 (VCC), MOD8.A4 (VCC), MOD8.A5 (VCC), MOD8.B1 (VCC), MOD8.B2 (VCC), MOD8.B3 (VCC), MOD8.B4 (VCC), MOD8.B5 (VCC), TP2.1

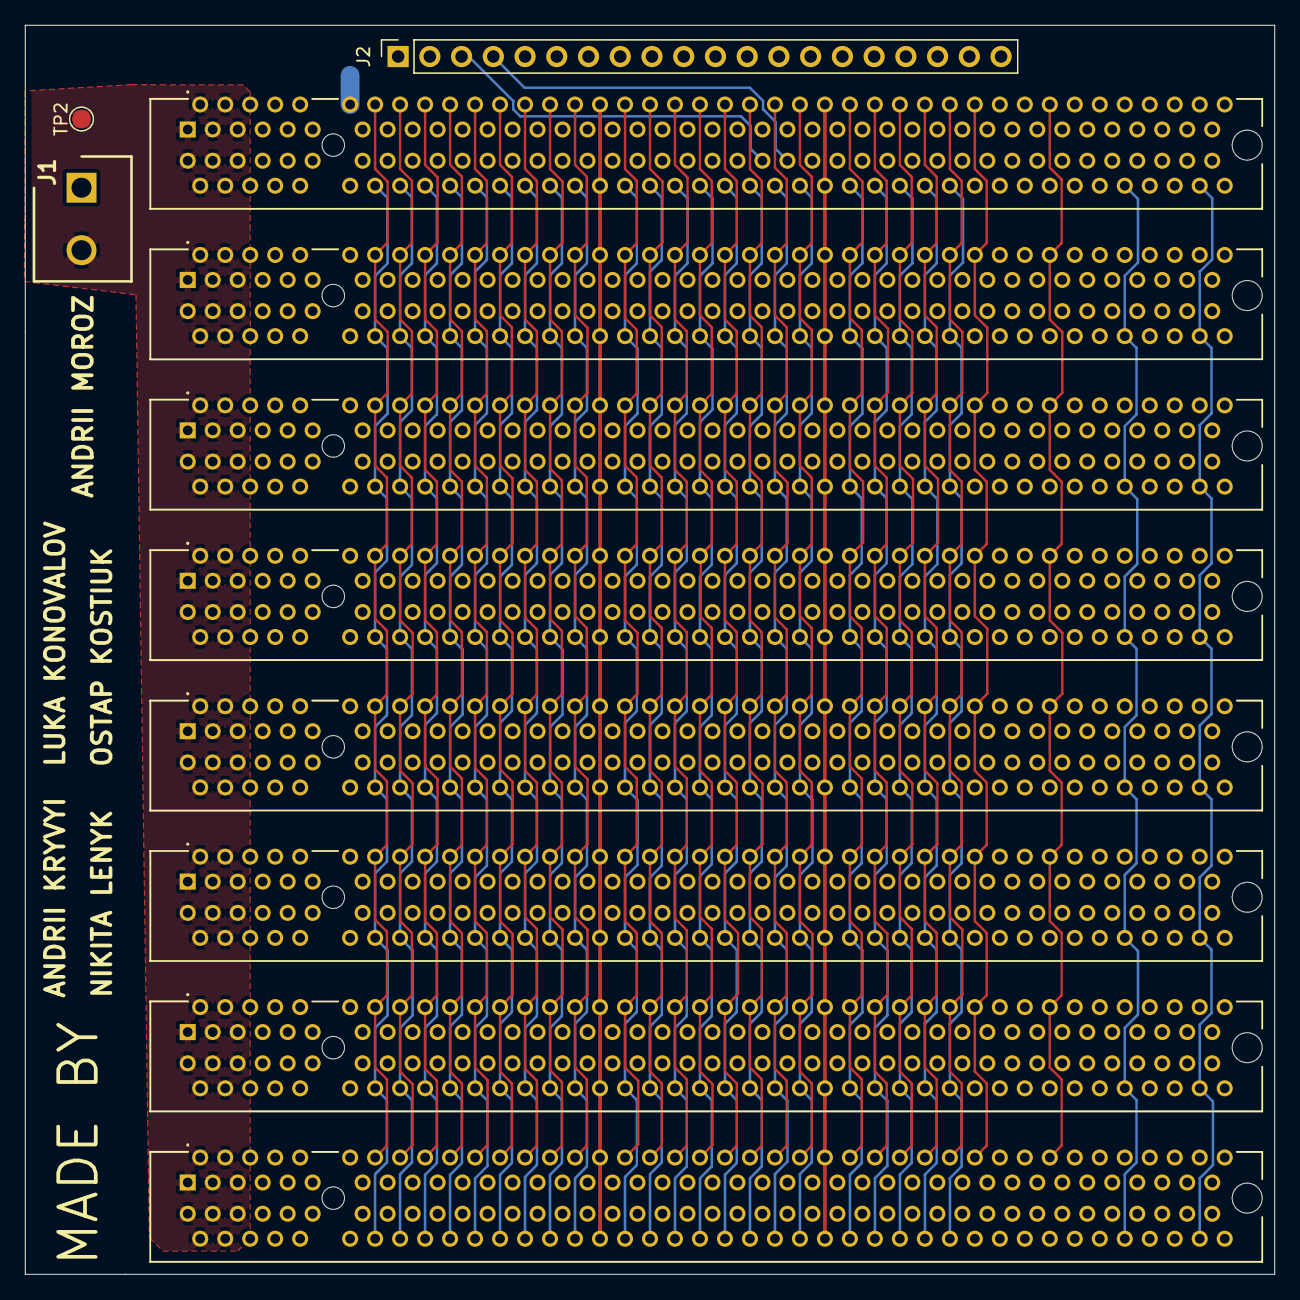
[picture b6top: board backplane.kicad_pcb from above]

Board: 4 copper layers, 100.0 x 100.0 mm, 12 parts (1 on the bottom side), 97 nets.
